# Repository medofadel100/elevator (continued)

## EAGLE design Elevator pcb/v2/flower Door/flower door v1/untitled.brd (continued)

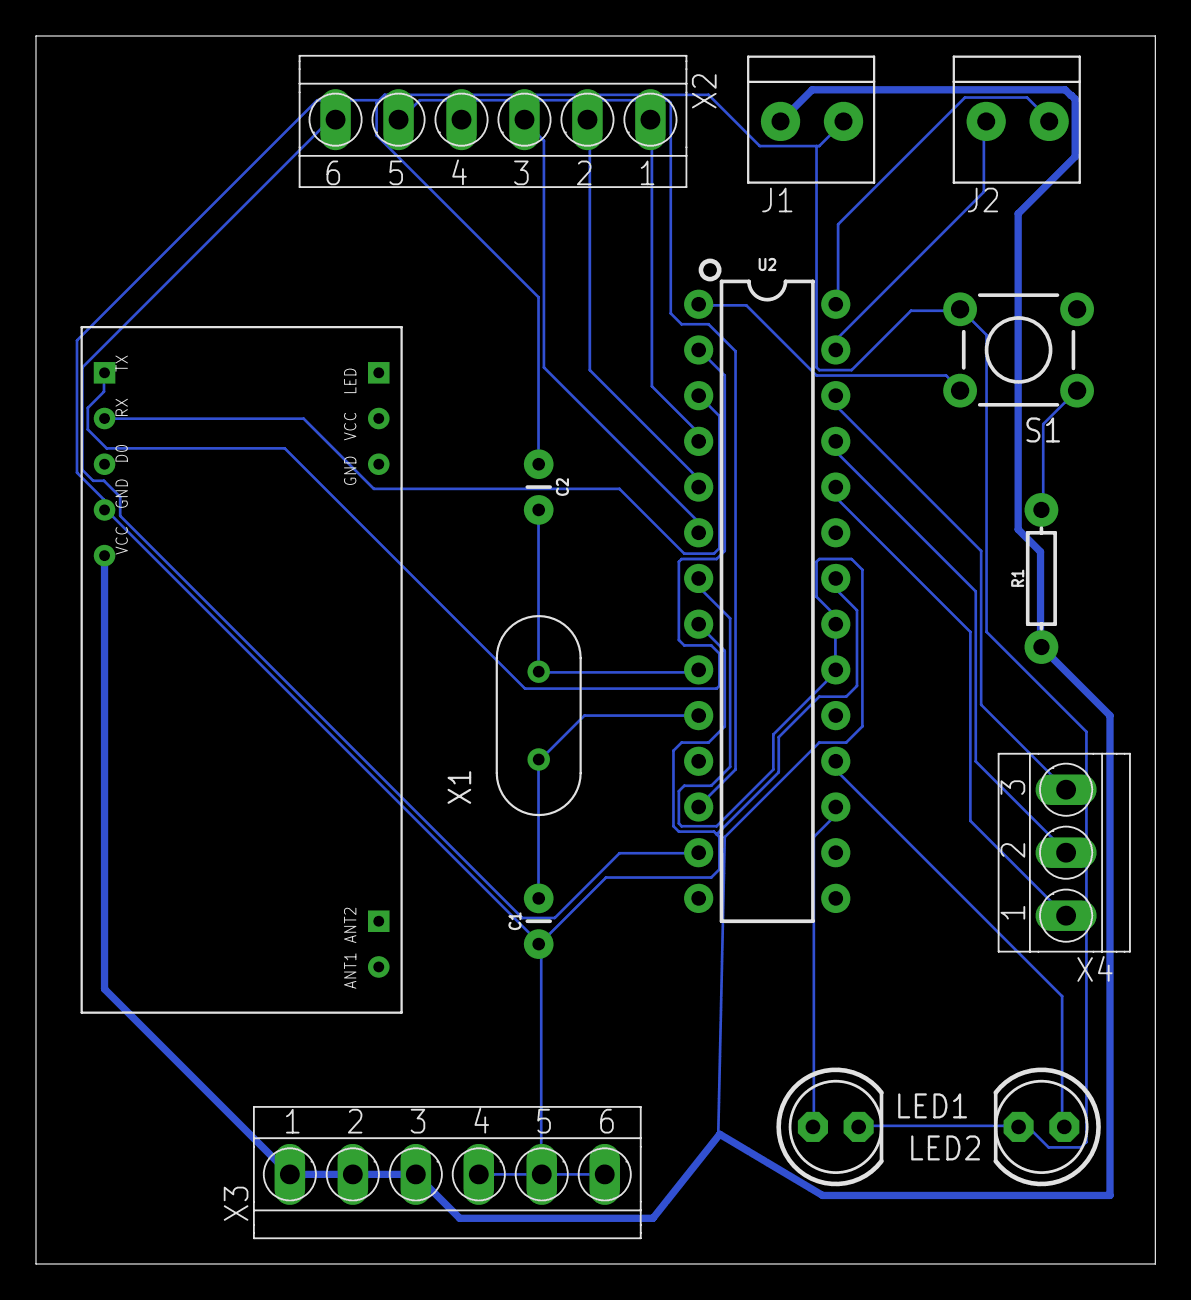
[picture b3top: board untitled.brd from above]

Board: 1 copper layer, 62.2 x 68.2 mm, 14 parts (0 on the bottom side), 20 nets.
